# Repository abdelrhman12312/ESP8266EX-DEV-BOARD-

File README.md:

you can view the board here : https://kicanvas.org/?github=https%3A%2F%2Fgithub.com%2Fabdelrhman12312%2FESP8266EX-DEV-BOARD-%2Ftree%2Fmain%2Fproject1

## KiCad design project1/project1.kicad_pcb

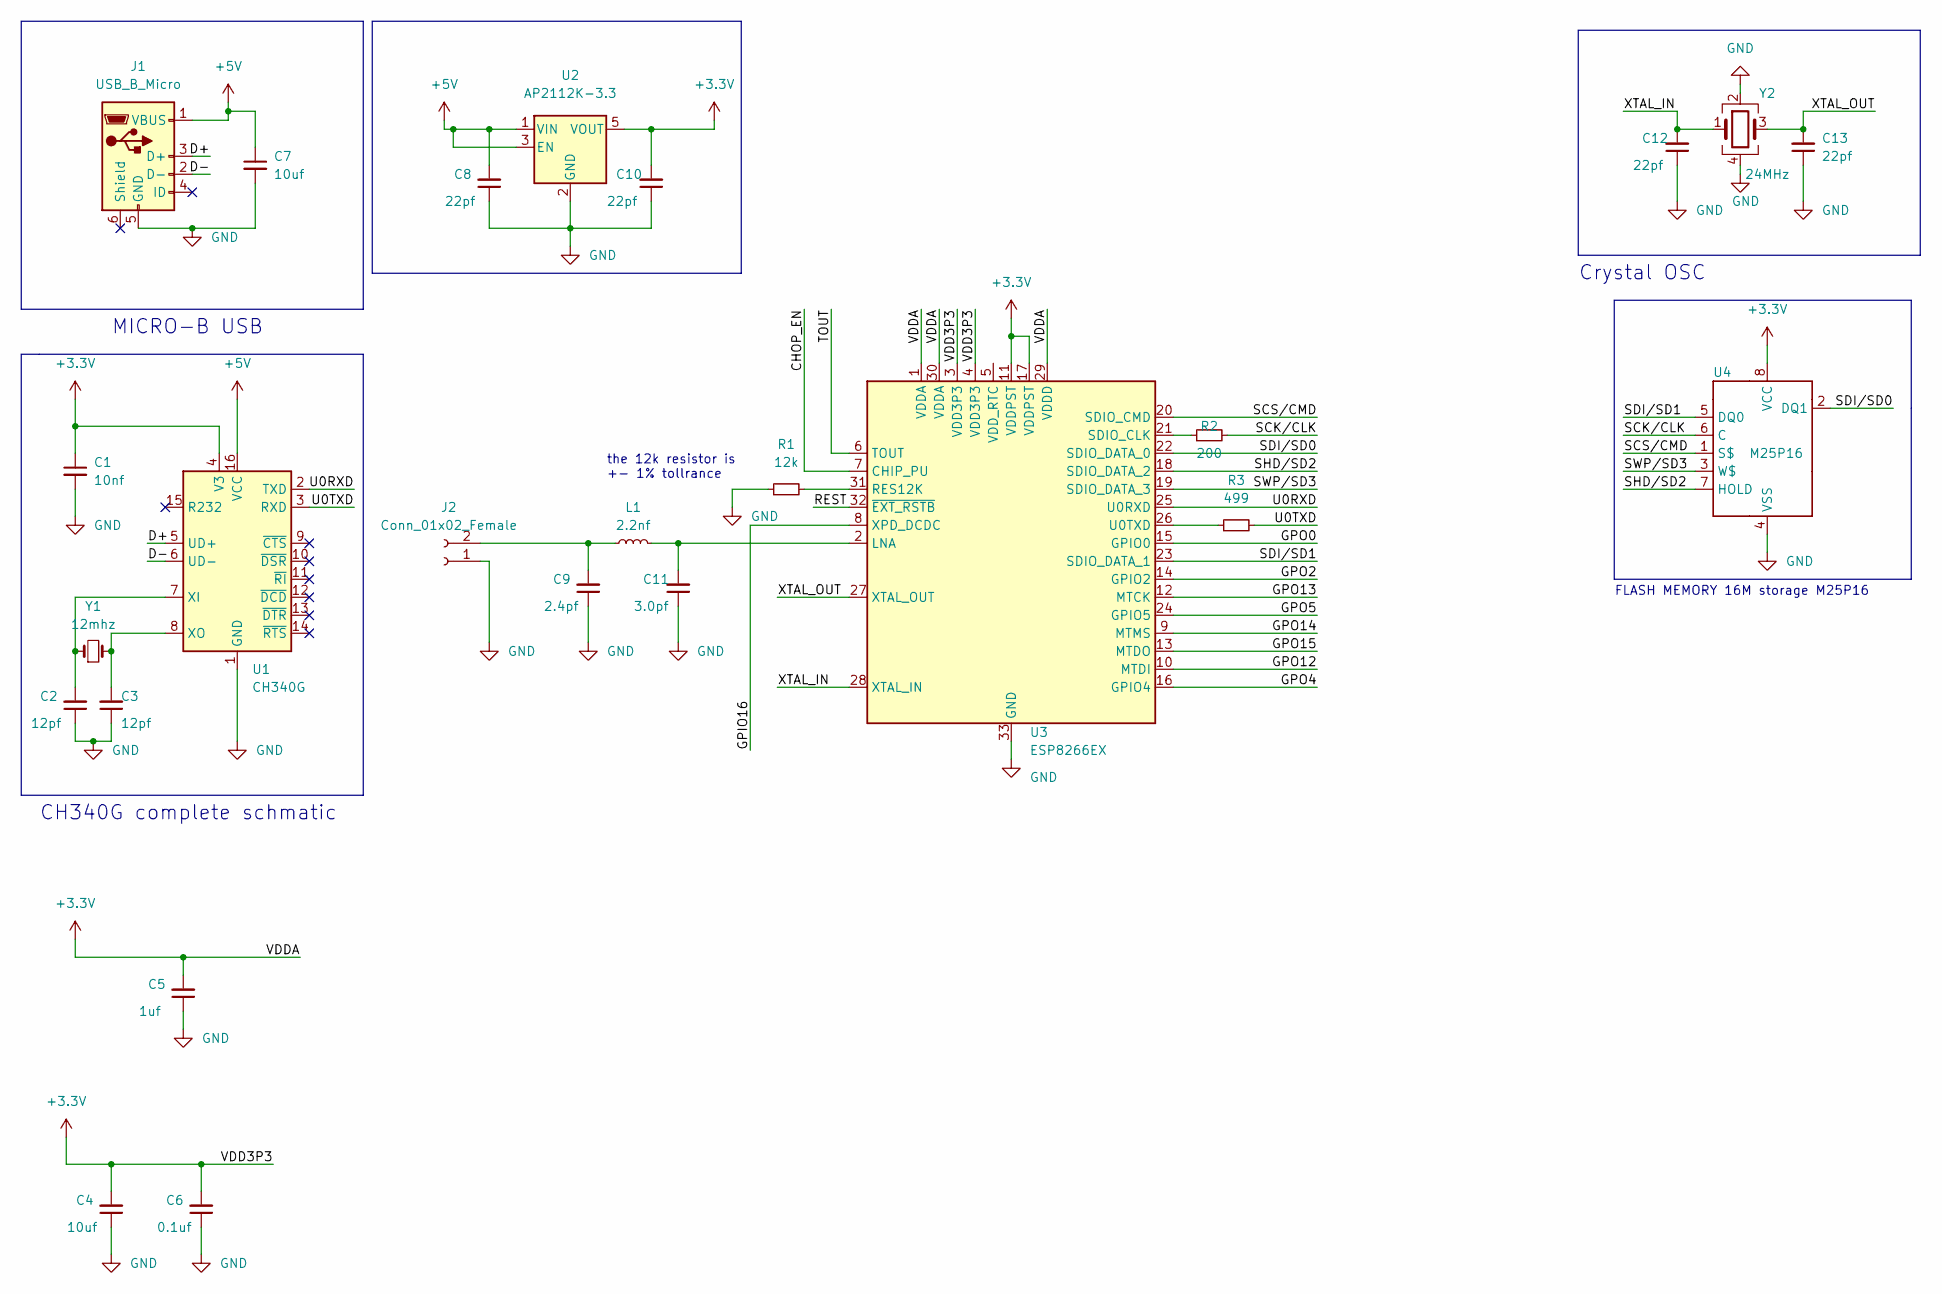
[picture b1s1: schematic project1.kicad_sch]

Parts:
C1: 10nf; C_0805_2012Metric_Pad1.18x1.45mm_HandSolder
C2, C3: 12pf; C_0805_2012Metric_Pad1.18x1.45mm_HandSolder
C4, C7: 10uf; C_0805_2012Metric_Pad1.18x1.45mm_HandSolder
C5: 1uf; C_0805_2012Metric_Pad1.18x1.45mm_HandSolder
C6: 0.1uf; C_0805_2012Metric_Pad1.18x1.45mm_HandSolder
C8, C10, C12, C13: 22pf; C_0805_2012Metric_Pad1.18x1.45mm_HandSolder
C9: 2.4pf; C_0805_2012Metric_Pad1.18x1.45mm_HandSolder
C11: 3.0pf; C_0805_2012Metric_Pad1.18x1.45mm_HandSolder
J1: USB_B_Micro; USB_Micro-B_GCT_USB3076-30-A
J2: Conn_01x02_Female; PCB_ANTENA1
L1: 2.2nf; C_0805_2012Metric_Pad1.18x1.45mm_HandSolder
R1: 12k; R_0805_2012Metric_Pad1.20x1.40mm_HandSolder
R2: 200; R_0805_2012Metric_Pad1.20x1.40mm_HandSolder
R3: 499; R_0805_2012Metric_Pad1.20x1.40mm_HandSolder
U1: CH340G; SOIC-16_3.9x9.9mm_P1.27mm
U2: AP2112K-3.3; SOT-23-5
U3: ESP8266EX; QFN-32-1EP_5x5mm_P0.5mm_EP3.45x3.45mm
U4: M25P16; MSOP-8_3x3mm_P0.65mm
Y1: 12mhz; Crystal_HC49-4H_Vertical
Y2: 24MHz; Crystal_SMD_Abracon_ABM3C-4Pin_5.0x3.2mm

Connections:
+3V3: C1.1, C4.2, C5.2, C6.2, C10.2, U1.4 (V3), U2.5 (VOUT), U3.1 (VDDA), U3.3 (VDD3P3), U3.4 (VDD3P3), U3.11 (VDDPST), U3.17 (VDDPST), U3.29 (VDDD), U3.30 (VDDA), U4.8 (VCC)
+5V: C7.1, C8.2, J1.1 (VBUS), U1.16 (VCC), U2.1 (VIN), U2.3 (EN)
/CHOP_EN: U3.7 (CHIP_PU)
/D+: J1.3 (D+), U1.5 (UD+)
/D-: J1.2 (D-), U1.6 (UD-)
/GPIO16: U3.8 (XPD_DCDC)
/GPO0: U3.15 (GPIO0)
/GPO2: U3.14 (GPIO2)
/GPO4: U3.16 (GPIO4)
/GPO5: U3.24 (GPIO5)
/GPO12: U3.10 (MTDI)
/GPO13: U3.12 (MTCK)
/GPO14: U3.9 (MTMS)
/GPO15: U3.13 (MTDO)
/REST: U3.32 (~EXT_RSTB)
/SCK/CLK: R2.2, U4.6 (C)
/SCS/CMD: U3.20 (SDIO_CMD), U4.1 (S$)
/SDI/SD0: U3.22 (SDIO_DATA_0), U4.2 (DQ1)
/SDI/SD1: U3.23 (SDIO_DATA_1), U4.5 (DQ0)
/SHD/SD2: U3.18 (SDIO_DATA_2), U4.7 (HOLD)
/SWP/SD3: U3.19 (SDIO_DATA_3), U4.3 (W$)
/TOUT: U3.6 (TOUT)
/U0RXD: U1.2 (TXD), U3.25 (U0RXD)
/U0TXD: R3.2, U1.3 (RXD)
/XTAL_IN: C12.2, U3.28 (XTAL_IN), Y2.1
/XTAL_OUT: C13.2, U3.27 (XTAL_OUT), Y2.3
GND: C1.2, C2.1, C3.1, C4.1, C5.1, C6.1, C7.2, C8.1, C9.1, C10.1, C11.1, C12.1, C13.1, J1.5 (GND), J2.1, R1.1, U1.1 (GND), U2.2 (GND), U3.33 (GND), U4.4 (VSS), Y2.2, Y2.4
unnamed: C2.2, U1.7 (XI), Y1.1
unnamed: C3.2, U1.8 (XO), Y1.2
unnamed: C9.2, J2.2, L1.1
unnamed: C11.2, L1.2, U3.2 (LNA)
unnamed: R1.2, U3.31 (RES12K)
unnamed: R2.1, U3.21 (SDIO_CLK)
unnamed: R3.1, U3.26 (U0TXD)

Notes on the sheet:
the 12k resistor is +- 1% tollrance
MICRO-B USB
CH340G complete schmatic
Crystal OSC
FLASH MEMORY 16M storage M25P16

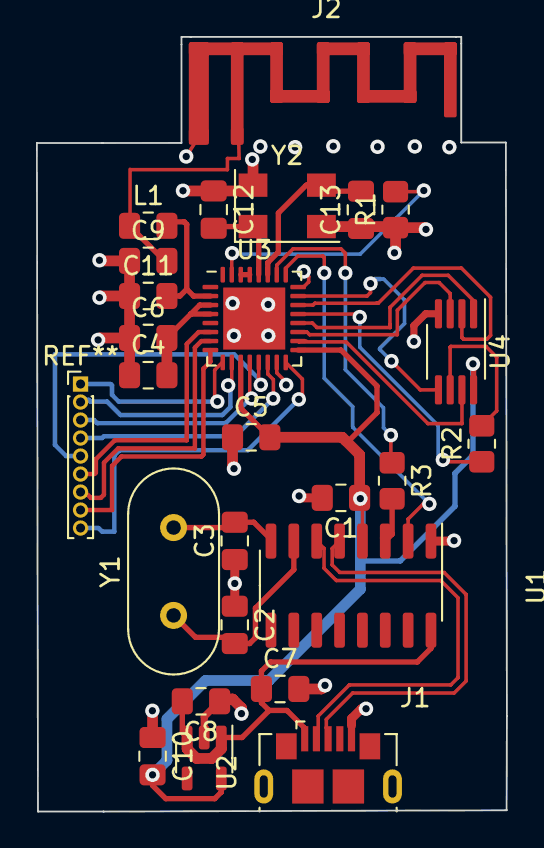
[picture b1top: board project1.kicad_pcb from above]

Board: 2 copper layers, 26.1 x 43.0 mm, 25 parts (0 on the bottom side), 22 nets.
